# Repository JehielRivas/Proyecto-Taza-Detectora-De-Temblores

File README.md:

<!DOCTYPE md>
<md>
<head>
      <title>Document</title>
</head>
<body>

<body>
</head>

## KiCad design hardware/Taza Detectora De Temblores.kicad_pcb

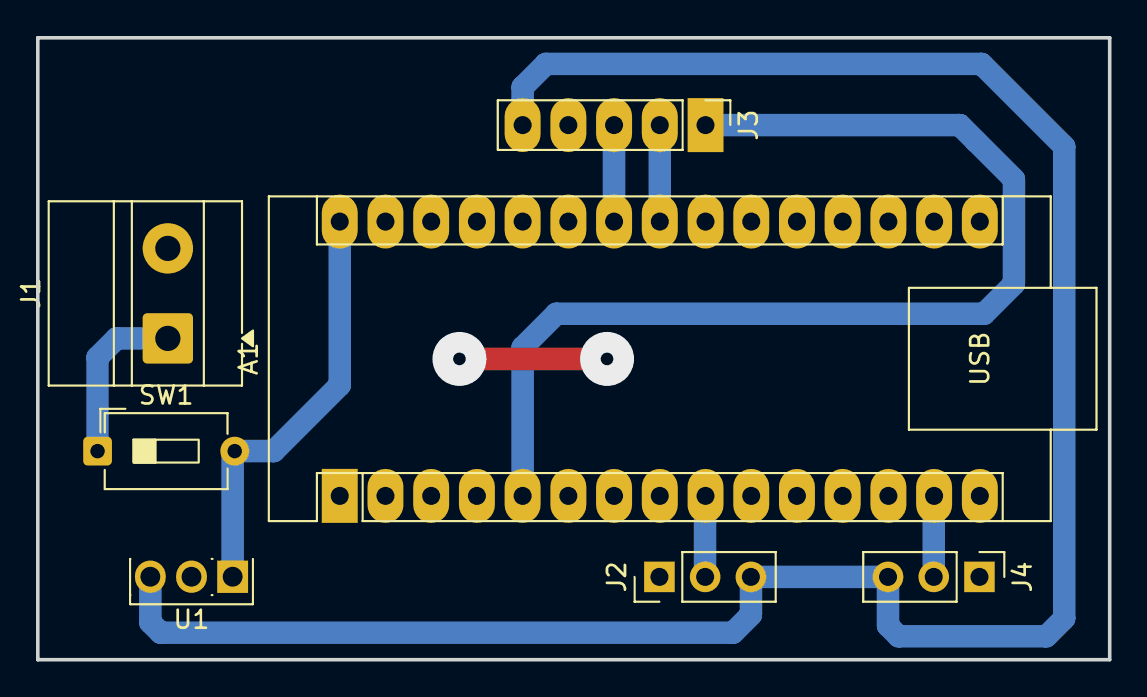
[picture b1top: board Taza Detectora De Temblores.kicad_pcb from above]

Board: 2 copper layers, 59.5 x 34.5 mm, 7 parts (0 on the bottom side), 9 nets.

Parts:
A1: Arduino_Nano_v2.x; Arduino_Nano
J1: ENTRADA; TerminalBlock_MetzConnect_Type011_RT05502HBLC_1x02_P5.00mm_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
J2, J4: Conn_01x03; PinHeader_1x03_P2.54mm_Vertical
J3: Conn_01x05; PinHeader_1x05_P2.54mm_Vertical
SW1: SW_DPST_x2; SW_DIP_SPSTx01_Slide_6.7x4.1mm_W7.62mm_P2.54mm_LowProfile
U1: L7805; SIPAK_Vertical

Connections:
+5V: J2.3, J3.5, J4.3, U1.3 (OUT)
+9V: A1.30 (VIN), SW1.2 (B), U1.1 (IN)
/INT: A1.5 (D2), J3.1
/SCL: A1.24 (A5), J3.3
/SDA: A1.23 (A4), J3.2
/SEÑAL 1: A1.9 (D6), J2.2
/SEÑAL 2: A1.14 (D11), J4.2
GND: A1.4 (GND), A1.29 (GND), J1.2, J2.1, J3.4, J4.1, U1.2 (GND)
unnamed: J1.1, SW1.1 (A)

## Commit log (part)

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2026-04-13 primer commit
2026-04-13 Create d.txt}
